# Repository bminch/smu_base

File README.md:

# smu_base
USB Source/Measure Unit Base Board

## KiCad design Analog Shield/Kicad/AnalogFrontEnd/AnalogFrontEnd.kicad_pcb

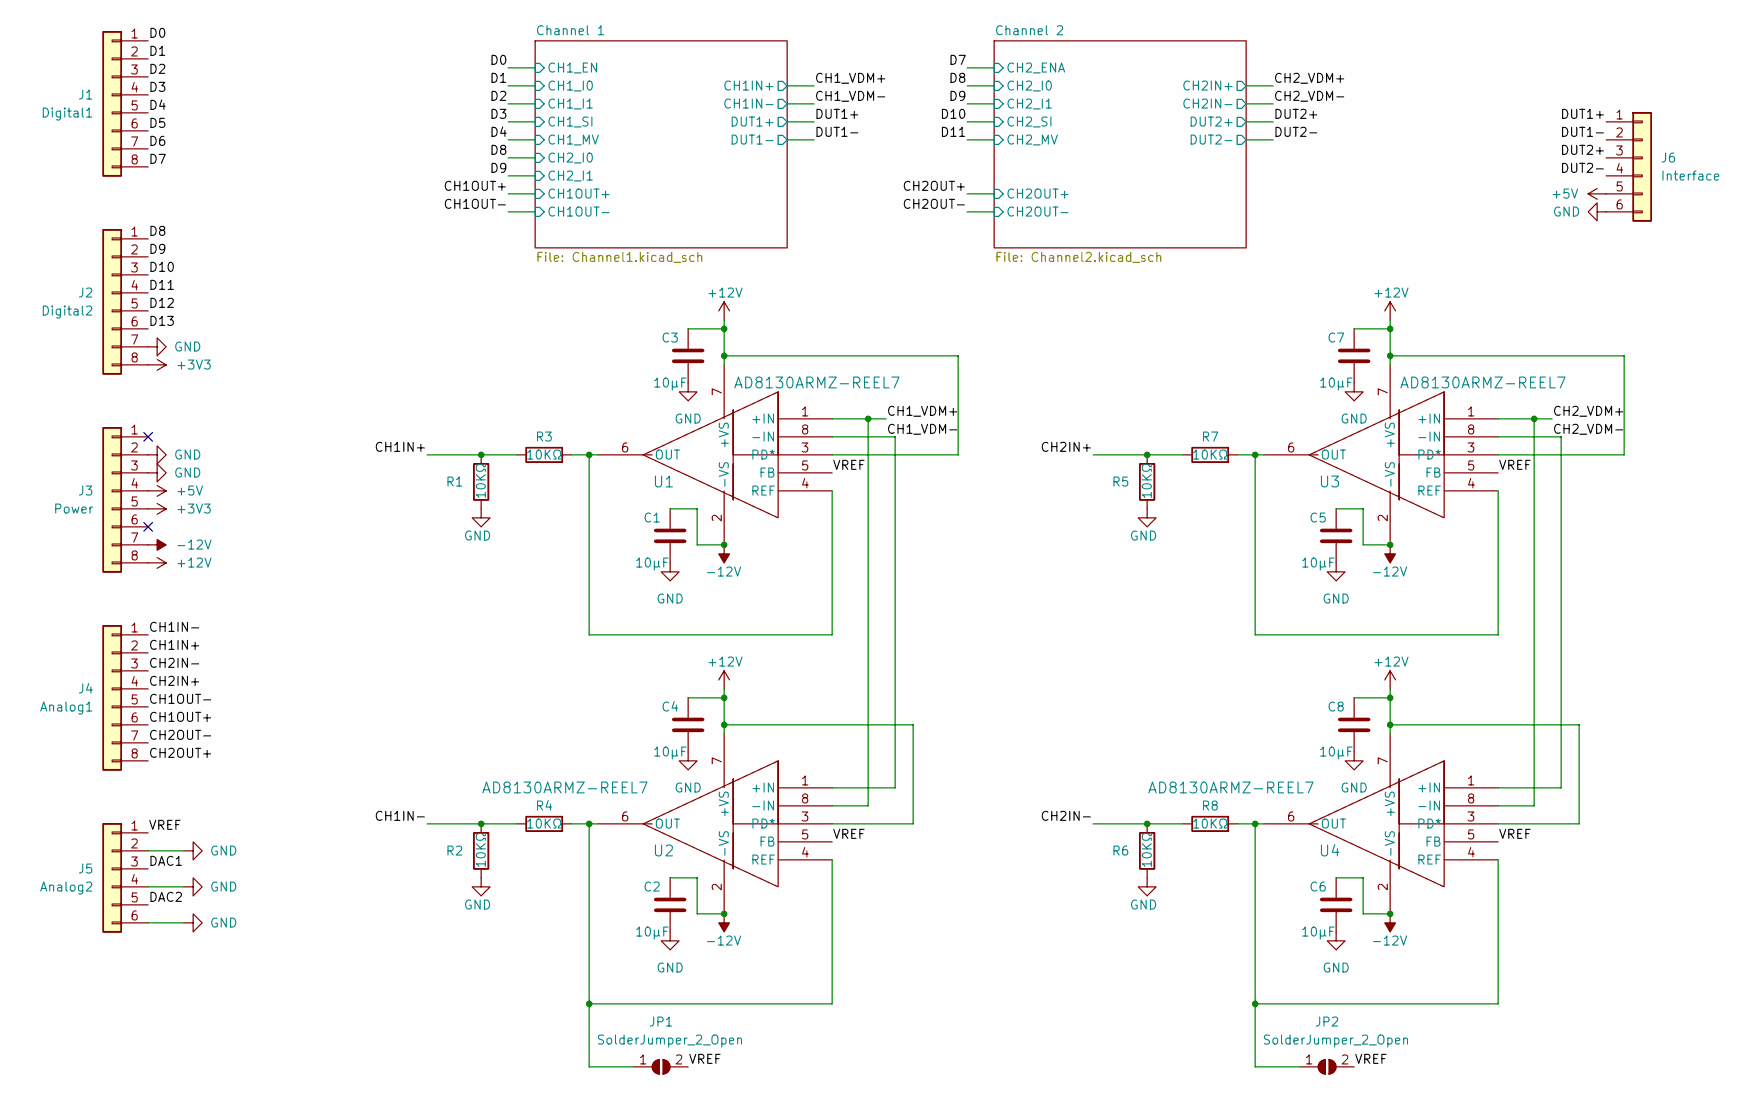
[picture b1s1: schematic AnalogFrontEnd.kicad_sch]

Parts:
C1, C2, C3, C4, C5, C6, C7, C8: 10μF; 0603
J1: Digital1; PinHeader_1x08_P2.54mm_Vertical
J2: Digital2; PinHeader_1x08_P2.54mm_Vertical
J3: Power; PinHeader_1x08_P2.54mm_Vertical
J4: Analog1; PinHeader_1x08_P2.54mm_Vertical
J5: Analog2; PinHeader_1x06_P2.54mm_Vertical
J6: Interface; PinHeader_1x06_P2.54mm_Vertical
JP1, JP2: SolderJumper_2_Open; SolderJumper-2_P1.3mm_Open_RoundedPad1.0x1.5mm
R1, R2, R3, R4, R5, R6, R7, R8: 10KΩ; 0603
U1, U2, U3, U4: AD8130ARMZ-REEL7; AD8130

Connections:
+3V3: J2.8, J3.5; also elsewhere on the board
+5V: J3.4, J6.5
+12V: C3.2, C4.2, C7.2, C8.2, J3.8, U1.3 (PD*), U1.7 (+VS), U2.3 (PD*), U2.7 (+VS), U3.3 (PD*), U3.7 (+VS), U4.3 (PD*), U4.7 (+VS); also elsewhere on the board
-12V: C1.2, C2.2, C5.2, C6.2, J3.7, U1.2 (-VS), U2.2 (-VS), U3.2 (-VS), U4.2 (-VS); also elsewhere on the board
/CH1IN+: J4.2, R1.2, R3.1
/CH1IN-: J4.1, R2.2, R4.1
/CH1OUT+: J4.6; also elsewhere on the board
/CH1OUT-: J4.5; also elsewhere on the board
/CH1_VDM+: U1.1 (+IN), U2.8 (-IN); also elsewhere on the board
/CH1_VDM-: U1.8 (-IN), U2.1 (+IN); also elsewhere on the board
/CH2IN+: J4.4, R5.2, R7.1
/CH2IN-: J4.3, R6.2, R8.1
/CH2OUT+: J4.8; also elsewhere on the board
/CH2OUT-: J4.7; also elsewhere on the board
/CH2_VDM+: U3.1 (+IN), U4.8 (-IN); also elsewhere on the board
/CH2_VDM-: U3.8 (-IN), U4.1 (+IN); also elsewhere on the board
/D0: J1.1; also elsewhere on the board
/D1: J1.2; also elsewhere on the board
/D2: J1.3; also elsewhere on the board
/D3: J1.4; also elsewhere on the board
/D4: J1.5; also elsewhere on the board
/D5: J1.6
/D6: J1.7
/D7: J1.8; also elsewhere on the board
/D8: J2.1; also elsewhere on the board
/D9: J2.2; also elsewhere on the board
/D10: J2.3; also elsewhere on the board
/D11: J2.4; also elsewhere on the board
/D12: J2.5
/D13: J2.6
/DAC1: J5.3
/DAC2: J5.5
/DUT1+: J6.1; also elsewhere on the board
/DUT1-: J6.2; also elsewhere on the board
/DUT2+: J6.3; also elsewhere on the board
/DUT2-: J6.4; also elsewhere on the board
/VREF: J5.1, JP1.2 (B), JP2.2 (B), U1.5 (FB), U2.5 (FB), U3.5 (FB), U4.5 (FB)
GND: C1.1, C2.1, C3.1, C4.1, C5.1, C6.1, C7.1, C8.1, J2.7, J3.2, J3.3, J5.2, J5.4, J5.6, J6.6, R1.1, R2.1, R5.1, R6.1; also elsewhere on the board
unnamed: JP1.1 (A), R4.2, U2.4 (REF), U2.6 (OUT)
unnamed: JP2.1 (A), R8.2, U4.4 (REF), U4.6 (OUT)
unnamed: R3.2, U1.4 (REF), U1.6 (OUT)
unnamed: R7.2, U3.4 (REF), U3.6 (OUT)

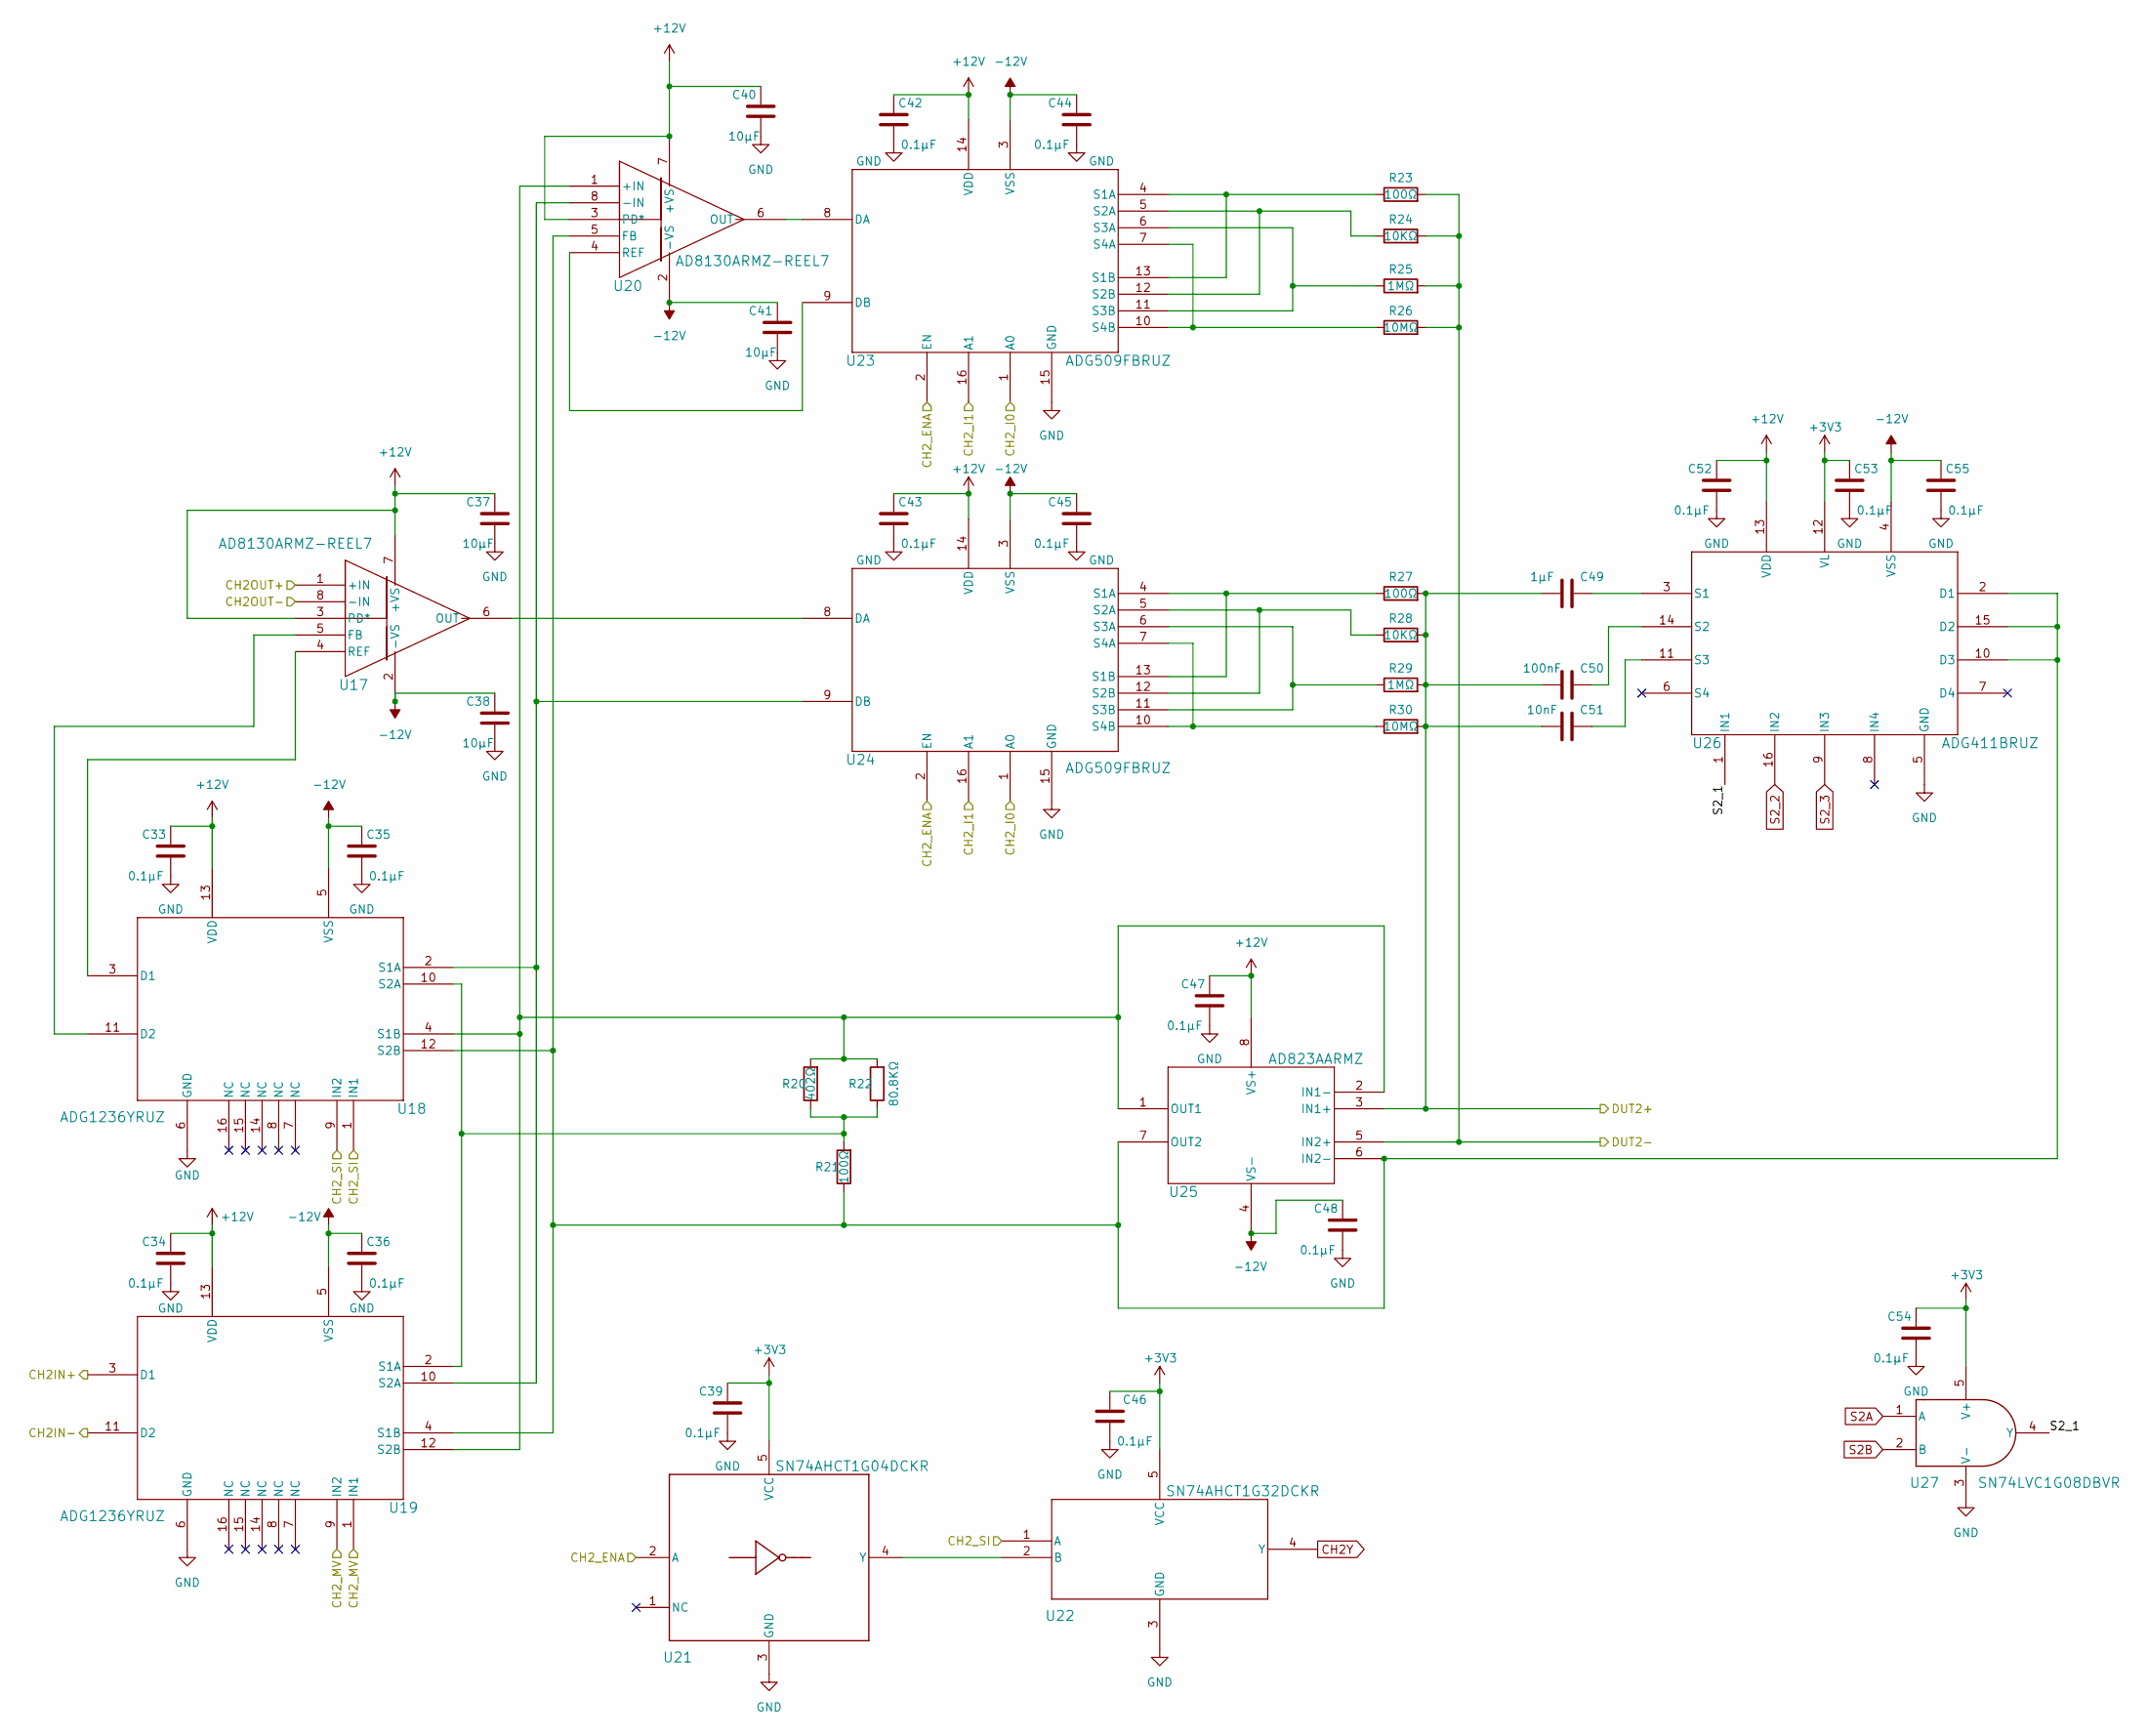
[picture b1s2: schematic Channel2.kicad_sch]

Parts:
C33, C34, C35, C36, C39, C42, C43, C44, C45, C46, C47, C48, C52, C53, C54, C55: 0.1μF; 0603
C37, C38, C40, C41: 10μF; 0603
C49: 1μF; 0603
C50: 100nF; 0603
C51: 10nF; 0603
R20: 402Ω; 0603
R21, R23, R27: 100Ω; 0603
R22: 80.8KΩ; 0603
R24, R28: 10KΩ; 0603
R25, R29: 1MΩ; 0603
R26, R30: 10MΩ; 1206
U17, U20: AD8130ARMZ-REEL7; AD8130
U18, U19: ADG1236YRUZ; ADG1236
U21: SN74AHCT1G04DCKR; SN74AHCT1G04
U22: SN74AHCT1G32DCKR; SN74AHCT1G32
U23, U24: ADG509FBRUZ; ADG509F
U25: AD823AARMZ; AD823
U26: ADG411BRUZ; ADG411
U27: SN74LVC1G08DBVR; SN74LVC1G08

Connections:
+3V3: C39.2, C46.2, C53.2, C54.2, U21.5 (VCC), U22.5 (VCC), U26.12 (VL), U27.5 (V+); also elsewhere on the board
+12V: C33.2, C34.2, C37.2, C40.2, C42.2, C43.2, C47.2, C52.2, U17.3 (PD*), U17.7 (+VS), U18.13 (VDD), U19.13 (VDD), U20.3 (PD*), U20.7 (+VS), U23.14 (VDD), U24.14 (VDD), U25.8 (VS+), U26.13 (VDD); also elsewhere on the board
-12V: C35.2, C36.2, C38.2, C41.2, C44.2, C45.2, C48.2, C55.2, U17.2 (-VS), U18.5 (VSS), U19.5 (VSS), U20.2 (-VS), U23.3 (VSS), U24.3 (VSS), U25.4 (VS-), U26.4 (VSS); also elsewhere on the board
/CH2OUT+: U17.1 (+IN); also elsewhere on the board
/CH2OUT-: U17.8 (-IN); also elsewhere on the board
/CH2_VDM+: U19.3 (D1); also elsewhere on the board
/CH2_VDM-: U19.11 (D2); also elsewhere on the board
/Channel 2/S2_1: U26.1 (IN1), U27.4 (Y)
/D7: U21.2 (A), U23.2 (EN), U24.2 (EN); also elsewhere on the board
/D8: U23.1 (A0), U24.1 (A0); also elsewhere on the board
/D9: U23.16 (A1), U24.16 (A1); also elsewhere on the board
/D10: U18.1 (IN1), U18.9 (IN2), U22.1 (A); also elsewhere on the board
/D11: U19.1 (IN1), U19.9 (IN2); also elsewhere on the board
/DUT2+: C49.1, C50.1, C51.1, R27.2, R28.2, R29.2, R30.2, U25.3 (IN1+); also elsewhere on the board
/DUT2-: R23.2, R24.2, R25.2, R26.2, U25.5 (IN2+); also elsewhere on the board
CH2Y: U22.4 (Y); also elsewhere on the board
GND: C33.1, C34.1, C35.1, C36.1, C37.1, C38.1, C39.1, C40.1, C41.1, C42.1, C43.1, C44.1, C45.1, C46.1, C47.1, C48.1, C52.1, C53.1, C54.1, C55.1, U18.6 (GND), U19.6 (GND), U21.3 (GND), U22.3 (GND), U23.15 (GND), U24.15 (GND), U26.5 (GND), U27.3 (V-); also elsewhere on the board
unnamed: C49.2, U26.3 (S1)
unnamed: C50.2, U26.14 (S2)
unnamed: C51.2, U26.11 (S3)
unnamed: R20.1, R21.2, R22.1, U18.10 (S2A), U19.2 (S1A)
unnamed: R20.2, R22.2, U18.4 (S1B), U19.12 (S2B), U20.1 (+IN), U25.1 (OUT1), U25.2 (IN1-)
unnamed: R21.1, U18.12 (S2B), U19.4 (S1B), U20.5 (FB), U25.6 (IN2-), U25.7 (OUT2), U26.2 (D1), U26.10 (D3), U26.15 (D2)
unnamed: R23.1, U23.4 (S1A), U23.13 (S1B)
unnamed: R24.1, U23.5 (S2A), U23.12 (S2B)
unnamed: R25.1, U23.6 (S3A), U23.11 (S3B)
unnamed: R26.1, U23.7 (S4A), U23.10 (S4B)
unnamed: R27.1, U24.4 (S1A), U24.13 (S1B)
unnamed: R28.1, U24.5 (S2A), U24.12 (S2B)
unnamed: R29.1, U24.6 (S3A), U24.11 (S3B)
unnamed: R30.1, U24.7 (S4A), U24.10 (S4B)
unnamed: U17.4 (REF), U18.3 (D1)
unnamed: U17.5 (FB), U18.11 (D2)
unnamed: U17.6 (OUT), U24.8 (DA)
unnamed: U18.2 (S1A), U19.10 (S2A), U20.8 (-IN), U24.9 (DB)
unnamed: U20.4 (REF), U23.9 (DB)
unnamed: U20.6 (OUT), U23.8 (DA)
unnamed: U21.4 (Y), U22.2 (B)
S2A: U27.1 (A); also elsewhere on the board
S2B: U27.2 (B); also elsewhere on the board
S2_2: U26.16 (IN2); also elsewhere on the board
S2_3: U26.9 (IN3); also elsewhere on the board

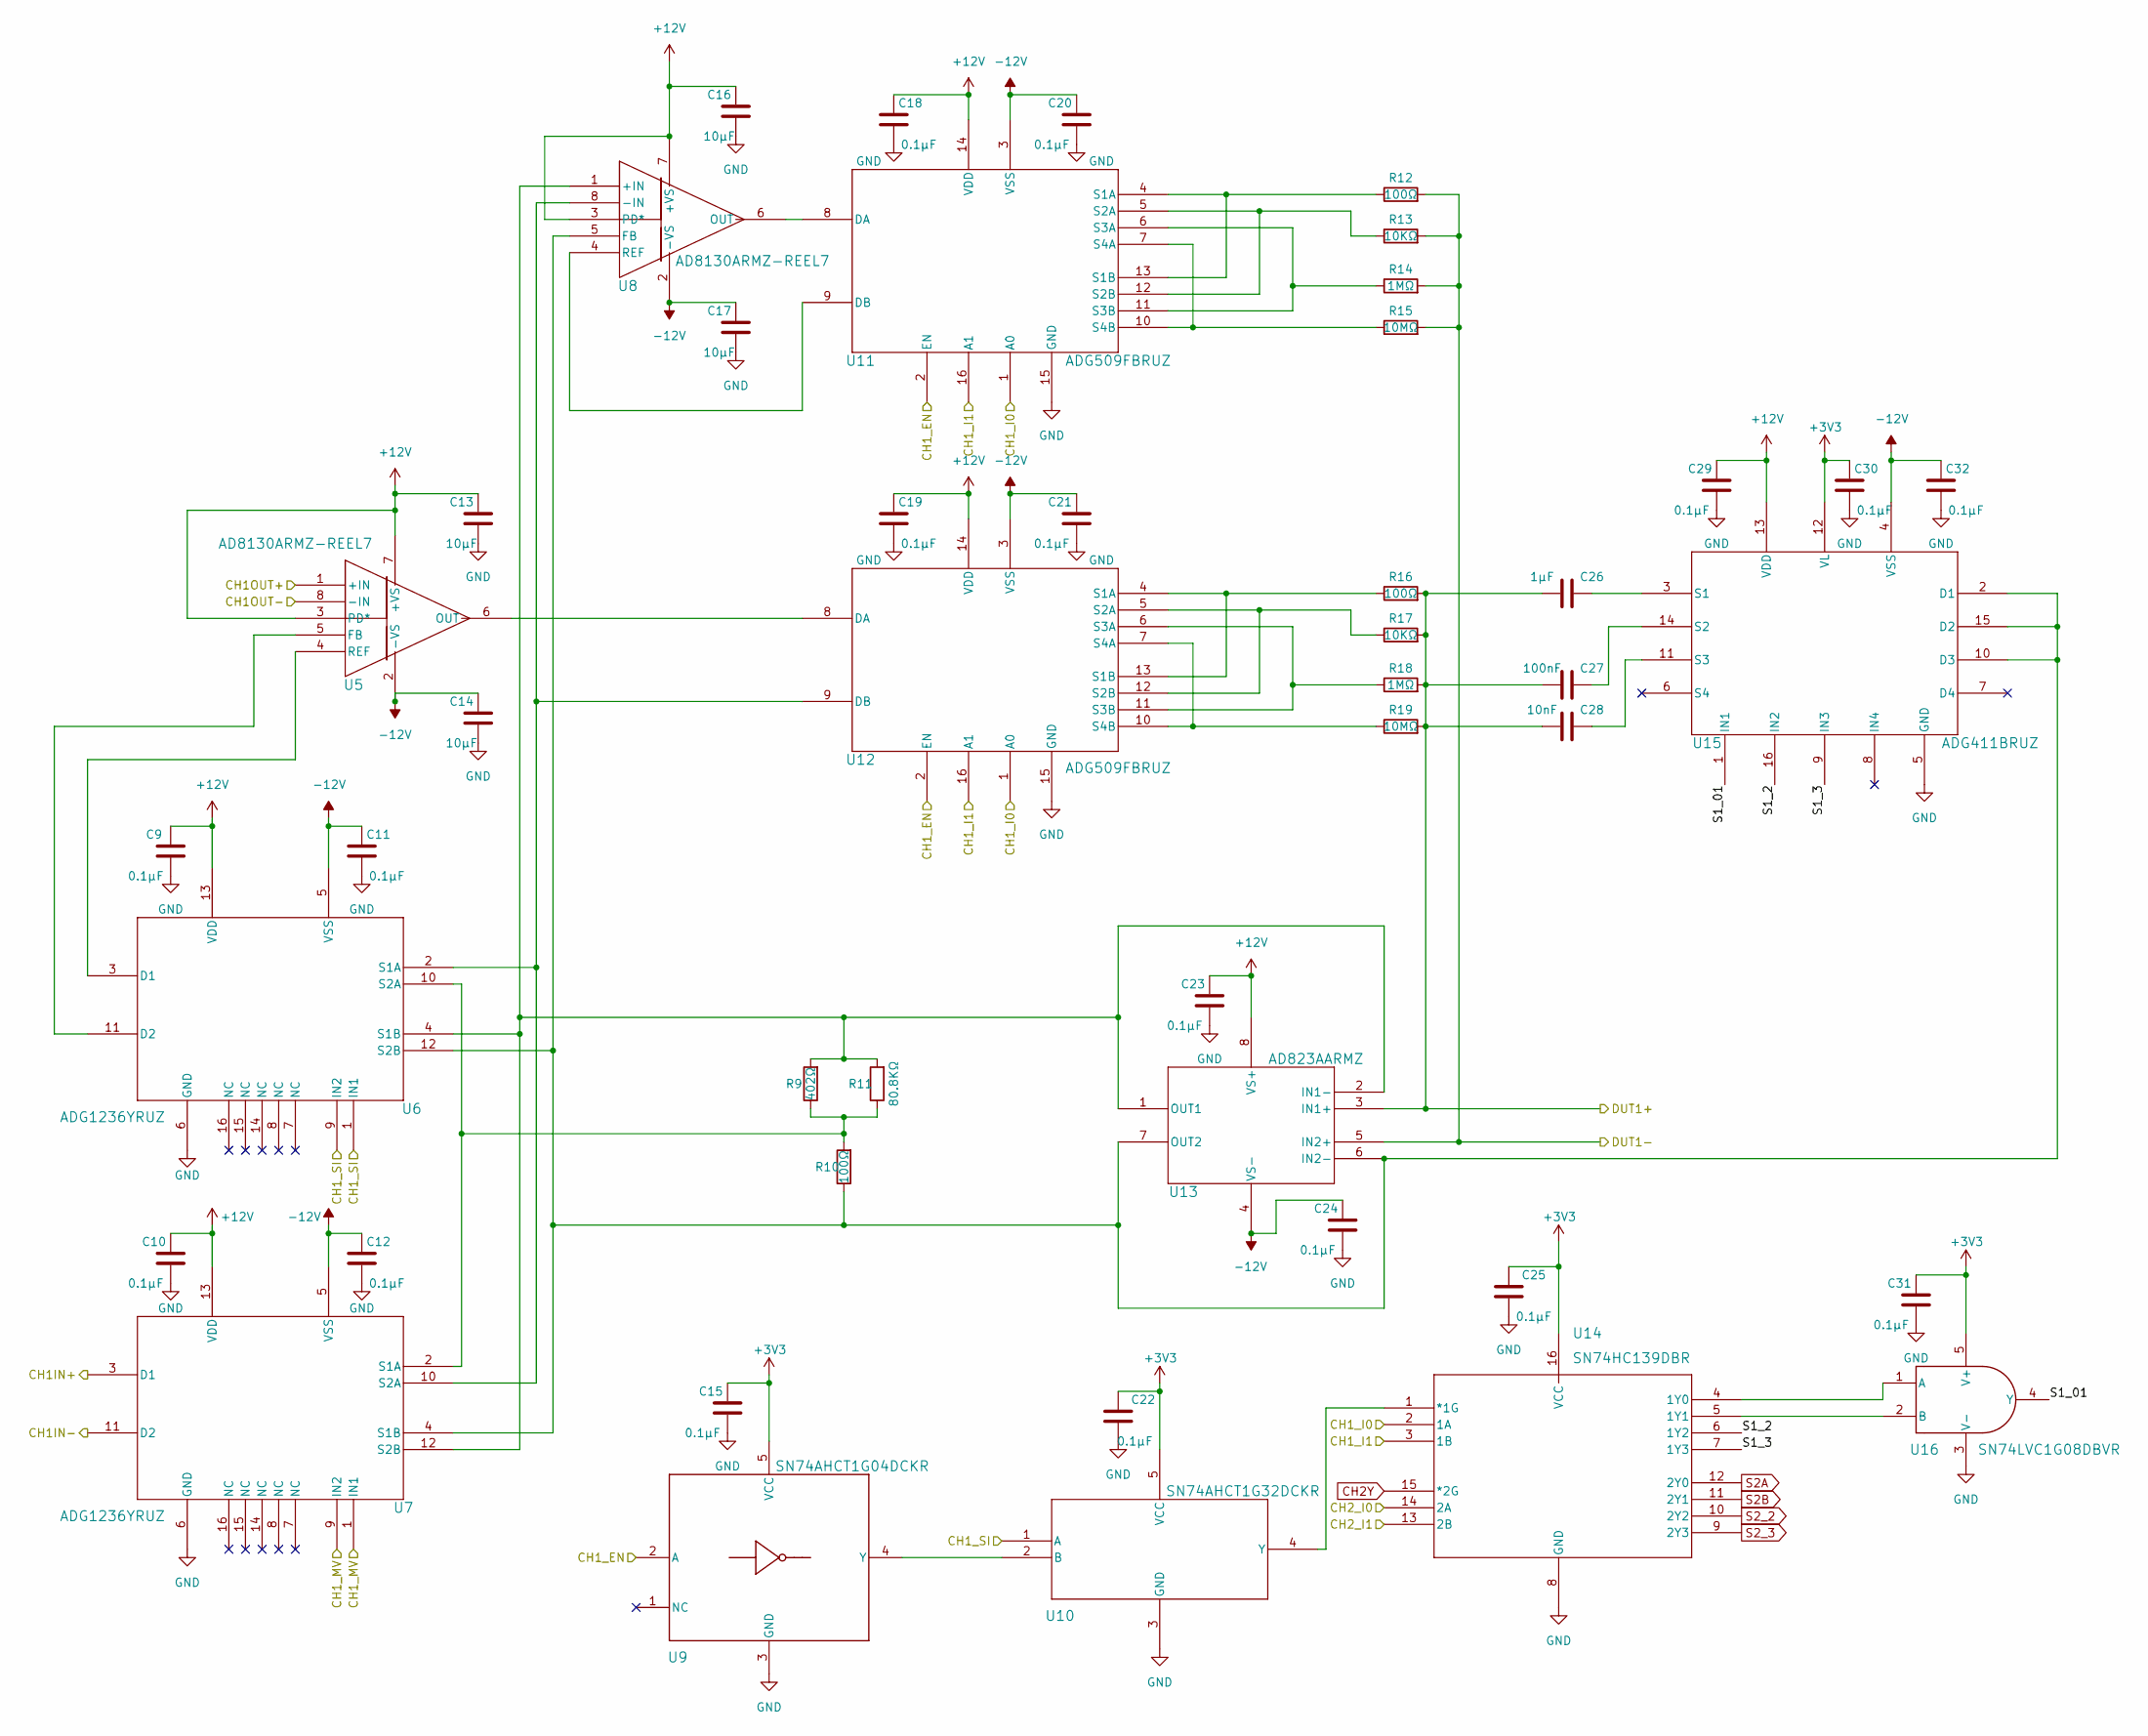
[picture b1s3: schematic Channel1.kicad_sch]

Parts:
C9, C10, C11, C12, C15, C18, C19, C20, C21, C22, C23, C24, C25, C29, C30, C31, C32: 0.1μF; 0603
C13, C14, C16, C17: 10μF; 0603
C26: 1μF; 0603
C27: 100nF; 0603
C28: 10nF; 0603
R9: 402Ω; 0603
R10, R12, R16: 100Ω; 0603
R11: 80.8KΩ; 0603
R13, R17: 10KΩ; 0603
R14, R18: 1MΩ; 0603
R15, R19: 10MΩ; 1206
U5, U8: AD8130ARMZ-REEL7; AD8130
U6, U7: ADG1236YRUZ; ADG1236
U9: SN74AHCT1G04DCKR; SN74AHCT1G04
U10: SN74AHCT1G32DCKR; SN74AHCT1G32
U11, U12: ADG509FBRUZ; ADG509F
U13: AD823AARMZ; AD823
U14: SN74HC139DBR; SN74HC139
U15: ADG411BRUZ; ADG411
U16: SN74LVC1G08DBVR; SN74LVC1G08

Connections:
+3V3: C15.2, C22.2, C25.2, C30.2, C31.2, U9.5 (VCC), U10.5 (VCC), U14.16 (VCC), U15.12 (VL), U16.5 (V+); also elsewhere on the board
+12V: C9.2, C10.2, C13.2, C16.2, C18.2, C19.2, C23.2, C29.2, U5.3 (PD*), U5.7 (+VS), U6.13 (VDD), U7.13 (VDD), U8.3 (PD*), U8.7 (+VS), U11.14 (VDD), U12.14 (VDD), U13.8 (VS+), U15.13 (VDD); also elsewhere on the board
-12V: C11.2, C12.2, C14.2, C17.2, C20.2, C21.2, C24.2, C32.2, U5.2 (-VS), U6.5 (VSS), U7.5 (VSS), U8.2 (-VS), U11.3 (VSS), U12.3 (VSS), U13.4 (VS-), U15.4 (VSS); also elsewhere on the board
/CH1OUT+: U5.1 (+IN); also elsewhere on the board
/CH1OUT-: U5.8 (-IN); also elsewhere on the board
/CH1_VDM+: U7.3 (D1); also elsewhere on the board
/CH1_VDM-: U7.11 (D2); also elsewhere on the board
/Channel 1/S1_01: U15.1 (IN1), U16.4 (Y)
/Channel 1/S1_2: U14.6 (1Y2), U15.16 (IN2)
/Channel 1/S1_3: U14.7 (1Y3), U15.9 (IN3)
/D0: U9.2 (A), U11.2 (EN), U12.2 (EN); also elsewhere on the board
/D1: U11.1 (A0), U12.1 (A0), U14.2 (1A); also elsewhere on the board
/D2: U11.16 (A1), U12.16 (A1), U14.3 (1B); also elsewhere on the board
/D3: U6.1 (IN1), U6.9 (IN2), U10.1 (A); also elsewhere on the board
/D4: U7.1 (IN1), U7.9 (IN2); also elsewhere on the board
/D8: U14.14 (2A); also elsewhere on the board
/D9: U14.13 (2B); also elsewhere on the board
/DUT1+: C26.1, C27.1, C28.1, R16.2, R17.2, R18.2, R19.2, U13.3 (IN1+); also elsewhere on the board
/DUT1-: R12.2, R13.2, R14.2, R15.2, U13.5 (IN2+); also elsewhere on the board
CH2Y: U14.15 (*2G); also elsewhere on the board
GND: C9.1, C10.1, C11.1, C12.1, C13.1, C14.1, C15.1, C16.1, C17.1, C18.1, C19.1, C20.1, C21.1, C22.1, C23.1, C24.1, C25.1, C29.1, C30.1, C31.1, C32.1, U6.6 (GND), U7.6 (GND), U9.3 (GND), U10.3 (GND), U11.15 (GND), U12.15 (GND), U14.8 (GND), U15.5 (GND), U16.3 (V-); also elsewhere on the board
unnamed: C26.2, U15.3 (S1)
unnamed: C27.2, U15.14 (S2)
unnamed: C28.2, U15.11 (S3)
unnamed: R10.1, U6.12 (S2B), U7.4 (S1B), U8.5 (FB), U13.6 (IN2-), U13.7 (OUT2), U15.2 (D1), U15.10 (D3), U15.15 (D2)
unnamed: R9.1, R10.2, R11.1, U6.10 (S2A), U7.2 (S1A)
unnamed: R9.2, R11.2, U6.4 (S1B), U7.12 (S2B), U8.1 (+IN), U13.1 (OUT1), U13.2 (IN1-)
unnamed: R12.1, U11.4 (S1A), U11.13 (S1B)
unnamed: R13.1, U11.5 (S2A), U11.12 (S2B)
unnamed: R14.1, U11.6 (S3A), U11.11 (S3B)
unnamed: R15.1, U11.7 (S4A), U11.10 (S4B)
unnamed: R16.1, U12.4 (S1A), U12.13 (S1B)
unnamed: R17.1, U12.5 (S2A), U12.12 (S2B)
unnamed: R18.1, U12.6 (S3A), U12.11 (S3B)
unnamed: R19.1, U12.7 (S4A), U12.10 (S4B)
unnamed: U5.4 (REF), U6.3 (D1)
unnamed: U5.5 (FB), U6.11 (D2)
unnamed: U9.4 (Y), U10.2 (B)
unnamed: U10.4 (Y), U14.1 (*1G)
unnamed: U8.6 (OUT), U11.8 (DA)
unnamed: U8.4 (REF), U11.9 (DB)
unnamed: U5.6 (OUT), U12.8 (DA)
unnamed: U6.2 (S1A), U7.10 (S2A), U8.8 (-IN), U12.9 (DB)
unnamed: U14.4 (1Y0), U16.1 (A)
unnamed: U14.5 (1Y1), U16.2 (B)
S2A: U14.12 (2Y0); also elsewhere on the board
S2B: U14.11 (2Y1); also elsewhere on the board
S2_2: U14.10 (2Y2); also elsewhere on the board
S2_3: U14.9 (2Y3); also elsewhere on the board

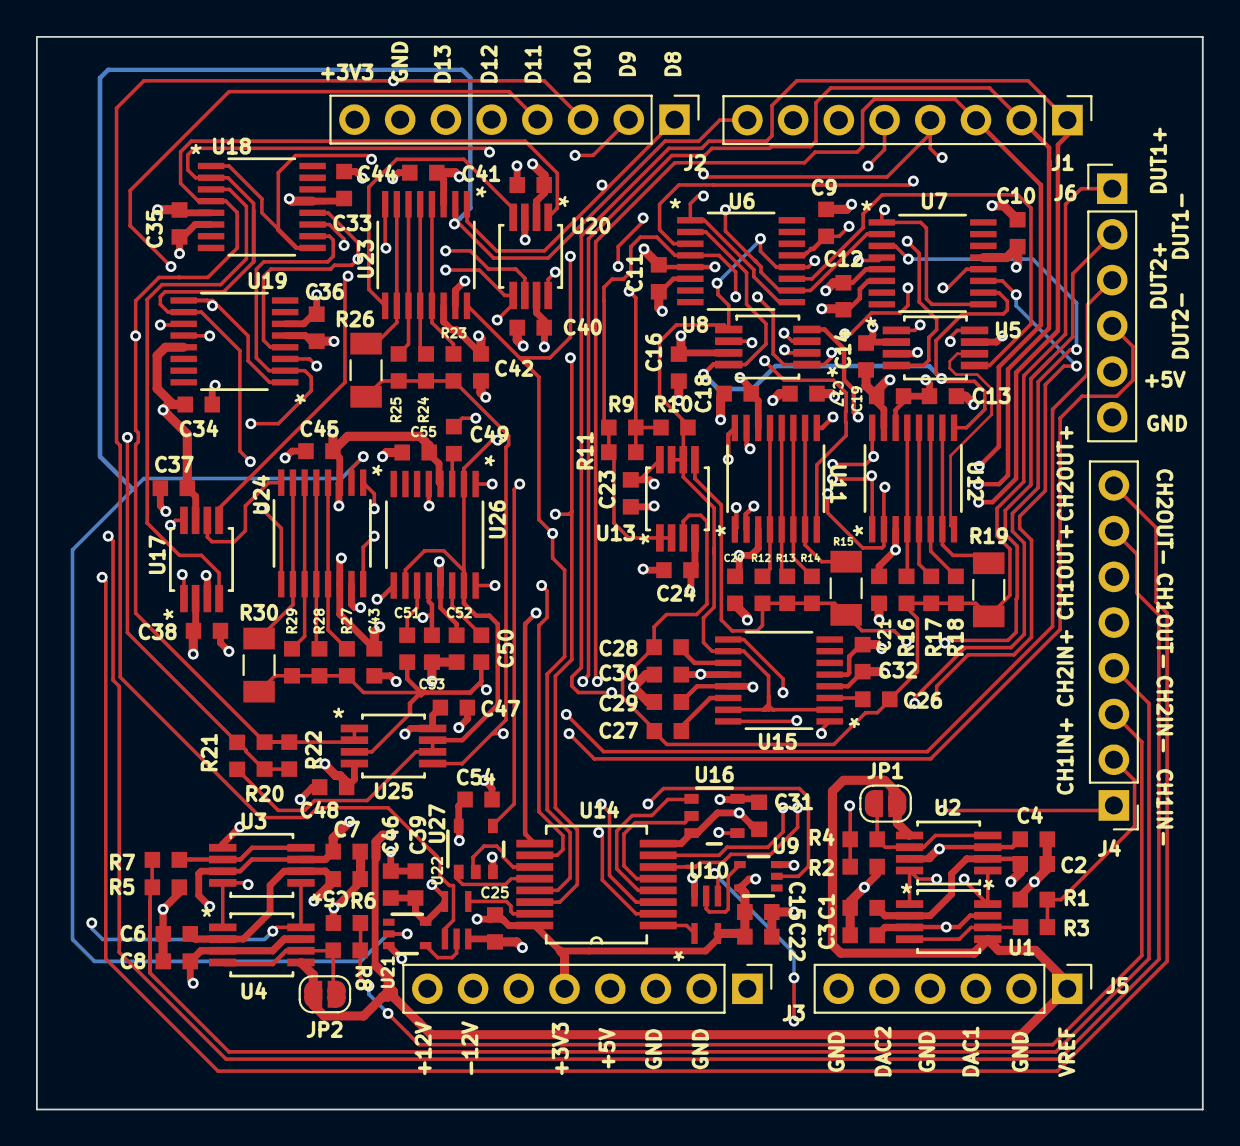
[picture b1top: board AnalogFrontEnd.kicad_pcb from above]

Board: 4 copper layers, 64.8 x 59.6 mm, 120 parts (0 on the bottom side), 90 nets.
